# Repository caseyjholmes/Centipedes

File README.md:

# Centipedes
Quad-purpose Manual and CV controlled 1-100 Burst Generator, Voltage Controlled Master Clock, Voltage Controlled Gate Crasher and Voltage Controlled Clock Mult/Divide Eurorack Module with PSI EITHER WAY power in 4HP.

The module utilizes a ATMEGA328P micrcontroller. The firmware is included before and after compile. You can program with arduino or AVRISPMKII or ebay clone.

Do not populate R19. You can if you want, but it's not necessary. 
Otherwise, this is a straight forward Eurorack format synthesizer module build. 

Enjoy! 
-Casey

5-22-2023 update
Centipedes will now be taking on four individual modes that work with the posted PCB. I will be posting four software routines for each. 
The first of which is a new Centipedes V3 Firmware. It will be uploaded today 5-22-23

There is now one mode for each software file set. No more easter eggs or hidden features. Each mode is stand alone face value. No menus or bugs.

Panels will be provided for each alternate software mode  

The first and updated software mode is NOW posted above on this page.                                                                             
The second, "Centipedes Voltage Controlled Matser Clock" and its associated front panel, is NOW available here:                                                                     
https://github.com/caseyjholmes/Centipedes_Master_Clock

The third mode, "Centipedes Voltage Controled Gate Crasher" and its associated alternate front panel is NOW available here:                                                                   
https://github.com/caseyjholmes/Centipedes_Gate_Crasher

The fourth mode, "Centipedes Voltage Controlled Clock Divider Multiplier" is SOON to be available here:                                                             
https://github.com/caseyjholmes/Centipedes_Clock_Mult_Div

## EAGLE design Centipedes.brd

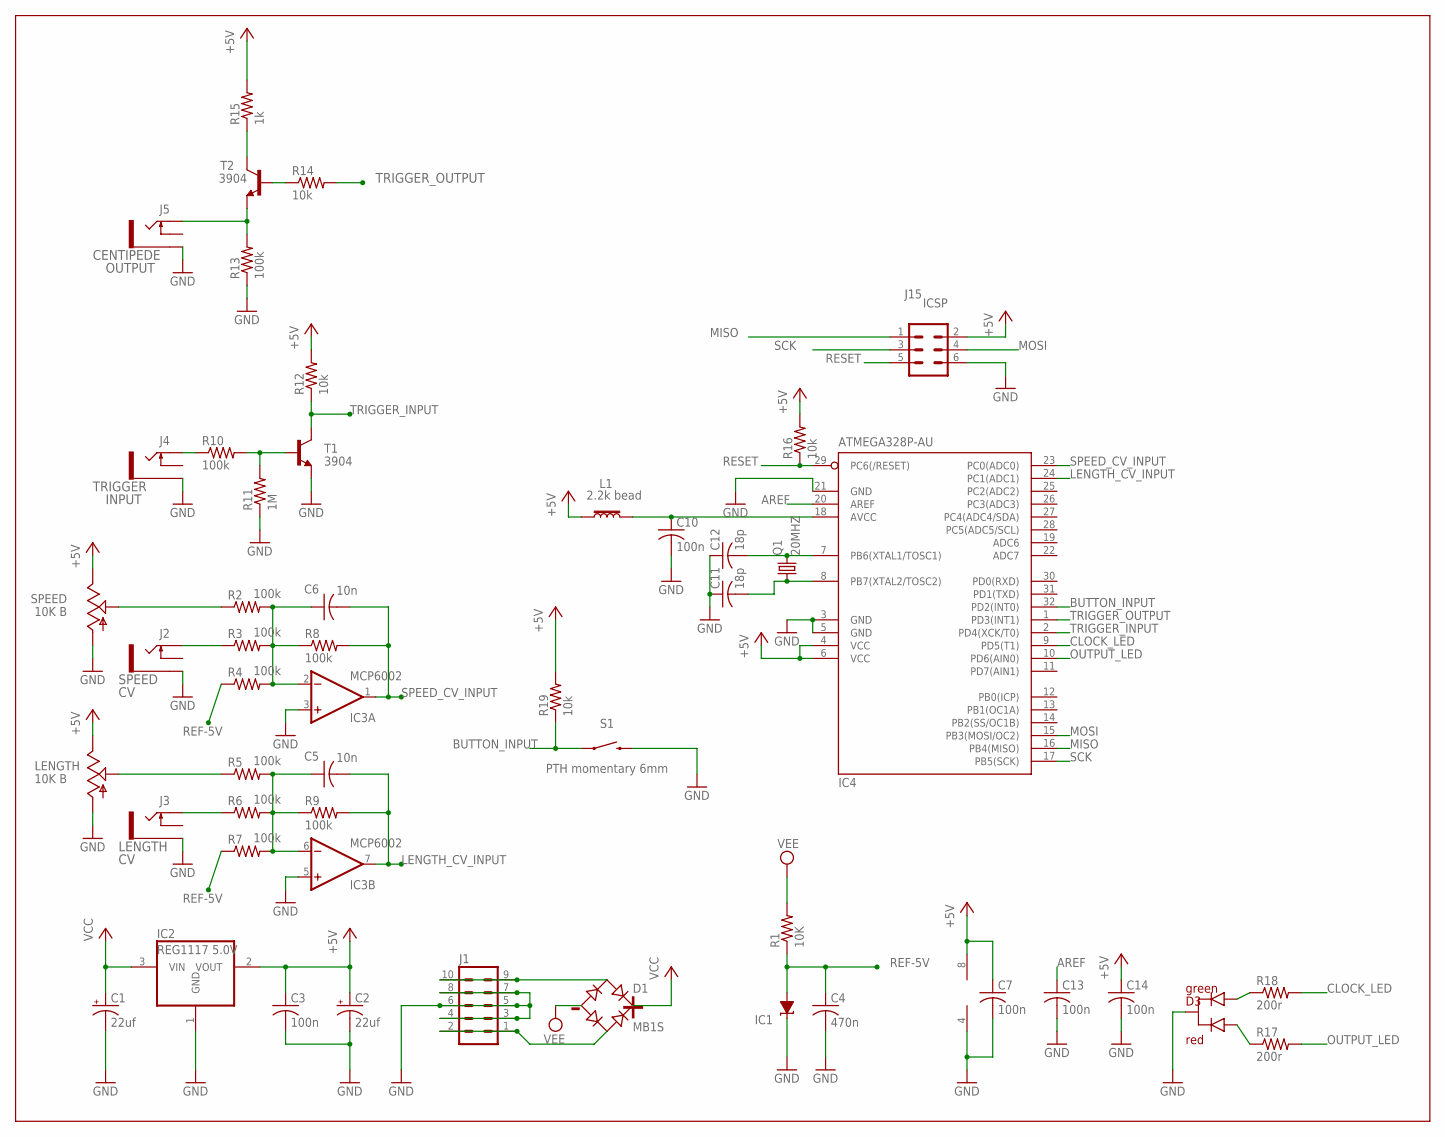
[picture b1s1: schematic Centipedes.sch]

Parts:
C1, C2: 22uf; PANASONIC_C
C3, C7, C10, C13, C14: 100n; C0603K
C4: 470n; C0603K
C5, C6: 10n; C0603K
C11, C12: 18p; C0603K
D1: MB1S; SOIC-4
D3: LED-DUALCOLOR3MM-THROUGH-HOLE; LED-DUALCOLOR-3MM
IC1: LM4041A12DBZ; DBZ_R-PDSO-G3
IC2: REG1117 5.0V; SOT223
IC3: MCP6002; SO08
IC4: ATMEGA328P-AU; TQFP32-08
J1: MA05-2
J2, J3, J4, J5: THONKICONNNEW; WQP-PJ301M-12_JACK
J15: ICSP; MA03-2
L1: 2.2k bead; 0603
LENGTH: 10K B; 9MM_SNAP-IN_POT
Q1: 20MHZ; HC49UP
R1: 10K; R0603
R2, R3, R4, R5, R6, R7, R8, R9, R10, R13: 100k; R0603
R11: 1M; R0603
R12, R14, R16, R19: 10k; R0603
R15: 1k; R0603
R17, R18: 200r; R0603
S1: PTH momentary 6mm; TACTILE_SWITCH_PTH_6.0MM
SPEED: 10K B; 9MM_SNAP-IN_POT
T1, T2: 3904; SOT23-BEC

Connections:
+5V: C2.+, C3.1, C7.1, C14.1, IC2.2 (VOUT), IC3.8 (V+), IC4.4 (VCC), IC4.6 (VCC), J15.2, L1.1, LENGTH.3 (E), R12.2, R15.2, R16.2, R19.2, SPEED.3 (E)
AREF: C13.1, IC4.20 (AREF)
BUTTON_INPUT: IC4.32 (PD2(INT0)), R19.1, S1.1
CLOCK_LED: IC4.9 (PD5(T1)), R18.2
GND: C1.-, C2.-, C3.2, C4.2, C7.2, C10.2, C11.1, C12.1, C13.2, C14.2, D3.K, IC1.1 (C), IC2.1 (GND), IC3.3 (+IN), IC3.4 (V-), IC3.5 (+IN), IC4.3 (GND), IC4.5 (GND), IC4.21 (GND), J1.3, J1.4, J1.5, J1.6, J1.7, J1.8, J2.P$3_SLEEVE (SLEEVE), J3.P$3_SLEEVE (SLEEVE), J4.P$3_SLEEVE (SLEEVE), J5.P$3_SLEEVE (SLEEVE), J15.6, LENGTH.1 (A), R11.1, R13.1, S1.3 (2), SPEED.1 (A), T1.E; also elsewhere on the board
LENGTH_CV_INPUT: C5.2, IC3.7 (OUT), IC4.24 (PC1(ADC1)), R9.2
MISO: IC4.16 (PB4(MISO)), J15.1
MOSI: IC4.15 (PB3(MOSI/OC2)), J15.4
unnamed: LENGTH.2 (S), R5.1
unnamed: C5.1, IC3.6 (-IN), R5.2, R6.2, R7.2, R9.1
unnamed: J3.P$1_TIP (TIP), R6.1
unnamed: D1.~2 (AC2), J1.1, J1.2
unnamed: D1.~1 (AC1), J1.9, J1.10
unnamed: J4.P$1_TIP (TIP), R10.1
unnamed: C6.1, IC3.2 (-IN), R2.2, R3.2, R4.2, R8.1
unnamed: R10.2, R11.2, T1.B
unnamed: J2.P$1_TIP (TIP), R3.1
unnamed: R2.1, SPEED.2 (S)
unnamed: J5.P$1_TIP (TIP), R13.2, T2.E
unnamed: R15.1, T2.C
unnamed: R14.1, T2.B
unnamed: C12.2, IC4.7 (PB6(XTAL1/TOSC1)), Q1.2
unnamed: C11.2, IC4.8 (PB7(XTAL2/TOSC2)), Q1.1
unnamed: D3.A1, R18.1
unnamed: C10.1, IC4.18 (AVCC), L1.2
unnamed: D3.A2, R17.1
OUTPUT_LED: IC4.10 (PD6(AIN0)), R17.2
REF-5V: C4.1, IC1.2 (A), R1.1, R4.1, R7.1
RESET: IC4.29 (PC6(/RESET)), J15.5, R16.1
SCK: IC4.17 (PB5(SCK)), J15.3
SPEED_CV_INPUT: C6.2, IC3.1 (OUT), IC4.23 (PC0(ADC0)), R8.2
TRIGGER_INPUT: IC4.2 (PD4(XCK/T0)), R12.1, T1.C
TRIGGER_OUTPUT: IC4.1 (PD3(INT1)), R14.2
VCC: C1.+, D1.+, IC2.3 (VIN)
VEE: D1.-, R1.2; also elsewhere on the board

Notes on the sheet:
TRIGGER
SPEED
LENGTH
CENTIPEDE
OUTPUT
INPUT
red
green

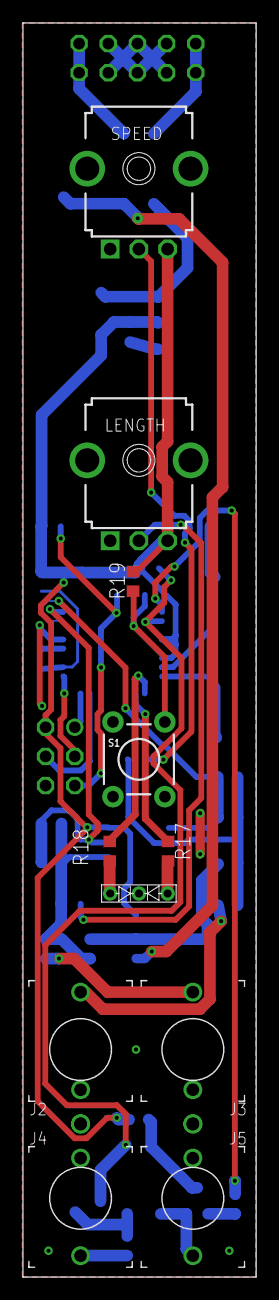
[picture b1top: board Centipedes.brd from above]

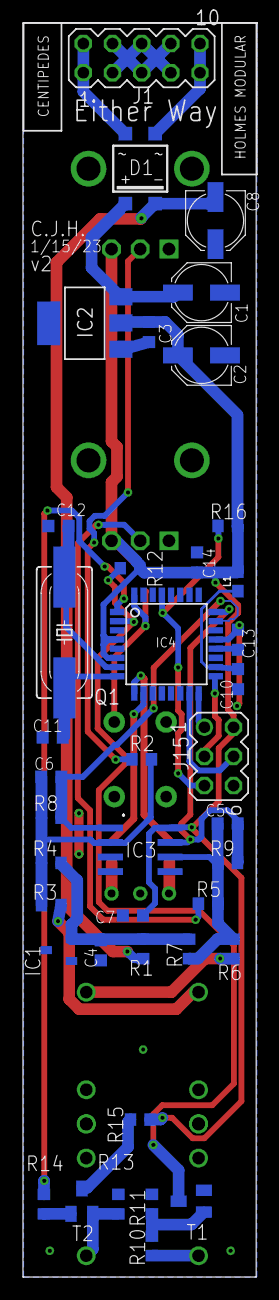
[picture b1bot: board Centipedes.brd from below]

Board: 2 copper layers, 20.3 x 109.2 mm, 51 parts (40 on the bottom side), 35 nets.

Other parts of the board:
C8: 22uf; PANASONIC_C

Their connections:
GND: C8.+; also elsewhere on the board
VEE: C8.-; also elsewhere on the board

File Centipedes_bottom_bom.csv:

Comment,Designator,Footprint,LCSC Part #
1M,IC1 R11,R0603,
1k,R15,R0603,
2.2k bead,L1,0603,
10K,R1,R0603,
10k,R12 R14 R16,R0603,
10n,C5 C6,C0603K,
18p,C11 C12,C0603K,
20MHZ,Q1,HC49UP,
22uf,C1 C2 C8,PANASONIC_C,
100k,R2 R3 R4 R5 R6 R7 R8 R9 R10 R13,R0603,
100n,C3 C7 C10 C13 C14,C0603K,
470n,C4,C0603K,
3904,T1 T2,SOT23-BEC,
ATMEGA328P-AU,IC4,TQFP32-08,
MB1S,D1,SOIC-4,
MCP6002,IC3,SO08,
REG1117 5.0V,IC2,SOT223,

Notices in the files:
parts and their libraries:
SparkFun-Coils: Licensing: Creative Commons ShareAlike 4.0 International - https://creativecommons.org/licenses/by-sa/4.0
